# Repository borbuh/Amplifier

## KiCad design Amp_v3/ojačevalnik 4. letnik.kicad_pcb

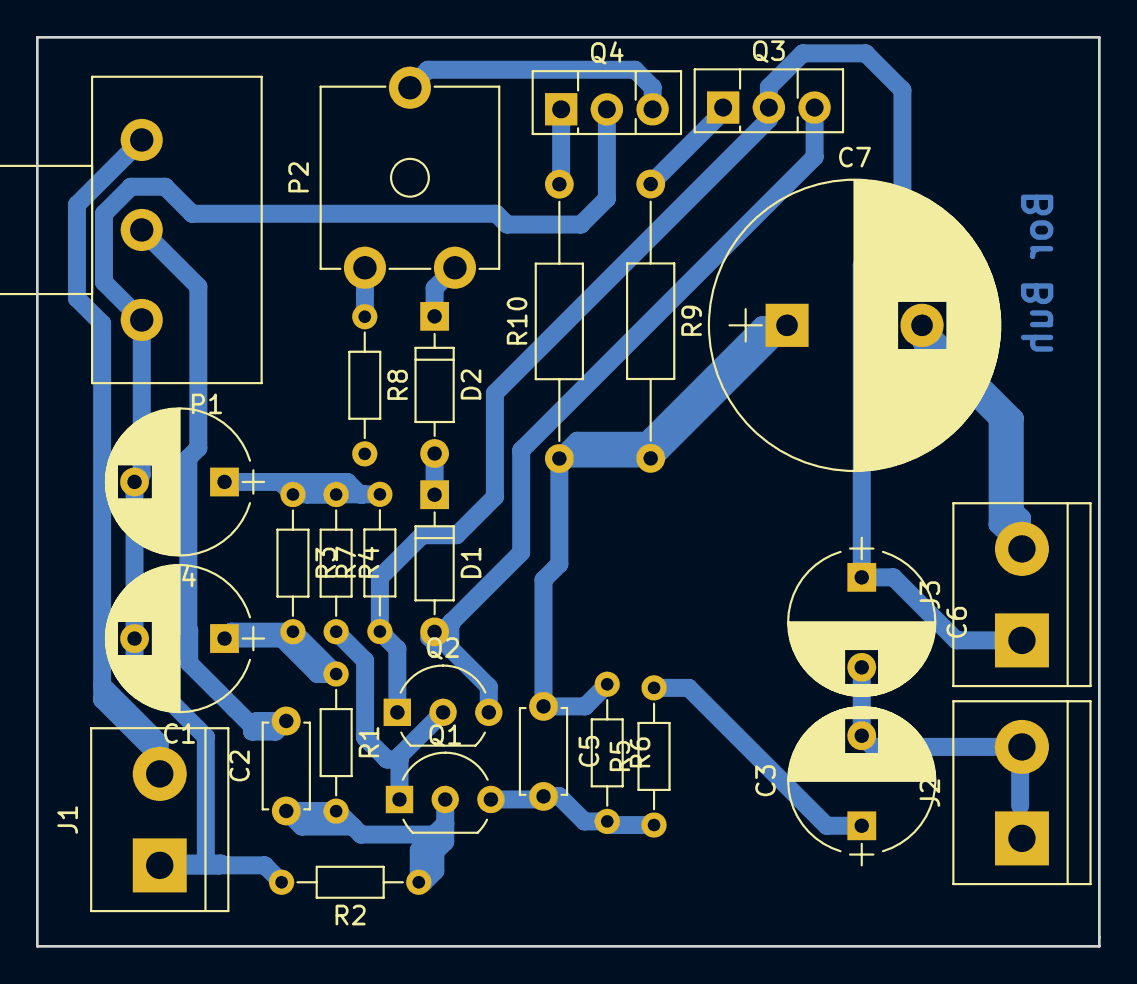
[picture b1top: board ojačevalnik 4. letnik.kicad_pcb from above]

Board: 2 copper layers, 59.0 x 50.5 mm, 28 parts (0 on the bottom side), 19 nets.

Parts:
C1: 470u; CP_Radial_D8.0mm_P5.00mm
C2: 100n; C_Disc_D4.7mm_W2.5mm_P5.00mm
C3: 330u; CP_Radial_D8.0mm_P5.00mm
C4: 220u; CP_Radial_D8.0mm_P5.00mm
C5: 150p; C_Disc_D4.7mm_W2.5mm_P5.00mm
C6: 100U; CP_Radial_D8.0mm_P5.00mm
C7: 220u; CP_Radial_D16.0mm_P7.50mm
D1, D2: 1N4148; D_DO-35_SOD27_P7.62mm_Horizontal
J1, J2, J3: Conn_01x02; bornier2
P1: 100K; Potentiometer_Omeg_PC16PU_Vertical
P2: 470; Potentiometer_Trimmer_ACP_CA9v_Horizontal_Px10.0mm_Py5.0mm
Q1: BC547; TO-92_Inline_Wide
Q2: Q_PNP_EBC; TO-92_Inline_Wide
Q3: BD139; TO-126_Vertical
Q4: BD140; TO-126_Vertical
R1, R3: 27k; R_Axial_DIN0204_L3.6mm_D1.6mm_P7.62mm_Horizontal
R2: 100k; R_Axial_DIN0204_L3.6mm_D1.6mm_P7.62mm_Horizontal
R4: 12k; R_Axial_DIN0204_L3.6mm_D1.6mm_P7.62mm_Horizontal
R5: 1k; R_Axial_DIN0204_L3.6mm_D1.6mm_P7.62mm_Horizontal
R6: 22k; R_Axial_DIN0204_L3.6mm_D1.6mm_P7.62mm_Horizontal
R7: 330; R_Axial_DIN0204_L3.6mm_D1.6mm_P7.62mm_Horizontal
R8: 1K8; R_Axial_DIN0204_L3.6mm_D1.6mm_P7.62mm_Horizontal
R9, R10: 1E; R_Axial_DIN0207_L6.3mm_D2.5mm_P15.24mm_Horizontal

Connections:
GND: C1.2, C3.2, C4.2, C6.2, J1.1, J2.1, J2.2, P1.3, Q4.2, R2.2, R8.2
unnamed: C1.1, R1.1, R3.2
unnamed: C2.1, Q1.2, R1.2, R2.1
unnamed: C2.2, P1.2
unnamed: C3.1, R5.2
unnamed: C4.1, R3.1, R4.1, R7.2
unnamed: C5.1, C7.1, R6.1, R9.2, R10.1
unnamed: C5.2, Q1.3, R5.1, R6.2
unnamed: C6.1, J3.1, Q2.1, Q3.2, R7.1
unnamed: C7.2, J3.2
unnamed: D1.1, D2.2
unnamed: D1.2, Q2.3, Q3.3
unnamed: D2.1, P2.1
unnamed: J1.2, P1.1
unnamed: P2.2, Q4.3
unnamed: P2.3, R8.1
unnamed: Q1.1, Q2.2, R4.2
unnamed: Q3.1, R9.1
unnamed: Q4.1, R10.2
